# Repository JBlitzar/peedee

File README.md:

# peedee

USB-C power delivery board

## What this project is and why I made it

It's a USB-C power delivery board. It uses just a bare CH224k with no MCU or other ICs, but it also offers convenience through its user interface,  which allows users to select voltage levels without needing to look at a complex silkscreen lookup table. Instead, I used a diode-matrix ROM to convert one-hot encoded voltage selections into the proper signals for the three binary configuration lines. The schematic is deceptively simple-- I had to translate the datasheet and invent the diode ROM. One unexpected tricky part of this project was *resistor sorting*. This is because peedee, as per the reference schematic, **doesn't use an LDO**. Instead, it uses a 1k resistor and a decoupling cap 💀. Uniquely though, PD can draw medium-high voltages and currents, so the resistor has to be well-rated. Not only that, but it needs to be SMD, a relatively small footprint, and in stock on LCSC. This constrains my resistor choices from potentially tens of thousands of listings to just a few. Anyways, that was interesting.

I also like how it ended up in such a small footprint-- about the size of the top half of your pinky finger. Part density is especially high though because most of the footprints are bigger than 0402. I made it long and skinny, and in this way, it seems like a natural extension of the long and skinny USB cable that powers it.

## PCB Images

## Overall BOM

|Item    |Cost |
|--------|-----|
|PCB     |2    |
|PCBA    |32.56|
|Shipping|3.3  |
|Taxes   |3    |
|Total   |40.86|

# Fabrication BOM

Looking for other fabrication outputs? This BOM in CSV form, plus the pnp files and gerbers, are in [PCB/peedee/production_real](PCB/peedee/production_real)

|Designator         |Footprint                          |Quantity|Value           |LCSC Part #|
|-------------------|-----------------------------------|--------|----------------|-----------|
|C1                 |C0603                              |1       |1uf             |C15849     |
|D10, D6, D7, D8, D9|SOD-123_L2.8-W1.8-LS3.7-RD-1       |5       |~               |C81598     |
|LED1               |LED0805-R-RD                       |1       |0805G           |C2297      |
|R1                 |R2010                              |1       |1k              |C2974087   |
|R2                 |R0603                              |1       |270Ω            |C22966     |
|SW1                |SW-SMD_TIMR-05-T-V-T-R             |1       |TIMR-05-T-V-T/R |C388479    |
|U1, U3, U4, U5     |R0805                              |4       |10k             |C17414     |
|U2                 |ESSOP-10_L4.9-W3.9-P1.0-LS6.0-TL-EP|1       |CH224K          |C970725    |
|USB1               |USB-C-SMD_TYPE-C-16PIN-2MD-073     |1       |TYPE-C 16PIN 2MD|C2765186   |

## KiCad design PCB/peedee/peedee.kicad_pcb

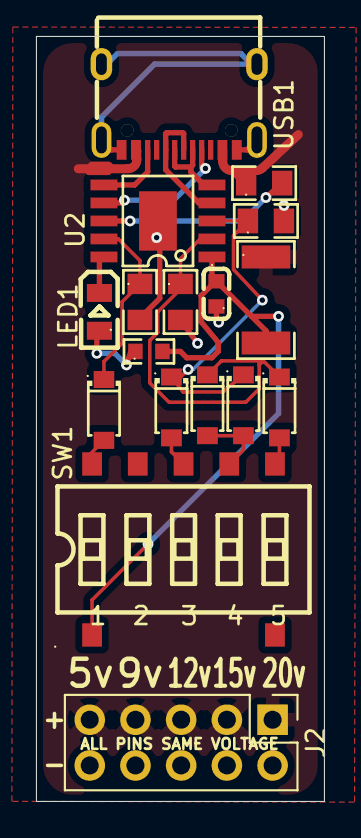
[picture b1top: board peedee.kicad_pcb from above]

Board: 2 copper layers, 16.0 x 42.5 mm, 17 parts (0 on the bottom side), 17 nets.

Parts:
C1: 1uf; C0603
D6, D7, D8, D9, D10: SOD-123_L2.8-W1.8-LS3.7-RD-1
J2: Conn_02x05_Odd_Even; PinHeader_2x05_P2.54mm_Vertical
LED1: 0805G; LED0805-R-RD
R1: 1k; R2010
R2: 270Ω; R0603
SW1: TIMR-05-T-V-T/R; SW-SMD_TIMR-05-T-V-T-R
U1, U3, U4, U5: 10k; R0805
U2: CH224K; ESSOP-10_L4.9-W3.9-P1.0-LS6.0-TL-EP
USB1: TYPE-C 16PIN 2MD; USB-C-SMD_TYPE-C-16PIN-2MD-073

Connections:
/CC1: U2.7 (CC1), USB1.A5 (CC1)
/CC2: U2.6 (CC2), USB1.B5 (CC2)
/CFG1: D6.1 (C), U2.9 (CFG1), U3.1
/CFG2: D8.1 (C), D9.1 (C), U2.2 (CFG2), U4.1
/CFG3: D7.1 (C), D10.1 (C), U2.3 (CFG3), U5.1
/D+: U2.4 (DP), USB1.A6 (Dp1), USB1.B6 (Dp2)
/D-: U2.5 (DM), USB1.A7 (Dn1), USB1.B7 (Dn2)
/PG: LED1.2 (K), U2.10 (PG)
/VBUS: J2.1, J2.3, J2.5, J2.7, J2.9, R1.1, U1.1, USB1.A4B9 (VBUS), USB1.B4A9 (VBUS)
/VDD: C1.2, R1.2, R2.2, SW1.1, U2.1 (VDD)
GND: C1.1, J2.2, J2.4, J2.6, J2.8, J2.10, U2.11 (GND), U3.2, U4.2, U5.2, USB1.13 (EH), USB1.14 (EH), USB1.A1B12 (GND), USB1.B1A12 (GND)
unnamed: D6.2 (A), SW1.7
unnamed: D7.2 (A), SW1.5
unnamed: D8.2 (A), SW1.3
unnamed: D9.2 (A), D10.2 (A), SW1.4
unnamed: LED1.1 (A), R2.1
unnamed: U1.2, U2.8 (VBUS)
